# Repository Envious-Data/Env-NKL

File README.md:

# Env-NKL
A Keyboard without Nav Keys but has A numpad!.. therefore NKL = NavKeyLess

## About
I saw a coolermaster quickfire TK and thought, ok well I could make my own of a similar layout and see how people like it, It also lets me have navkeys and numpad in a board similar to TKL in width so we'll see.

The board is designed to fit SMD Nuts so ill likely solder those onto this board when I get around to ordering my own.

Ive yet to create the firmware but you'll see it in the Repo if I does
keep in mind all my README's dont get updated often.

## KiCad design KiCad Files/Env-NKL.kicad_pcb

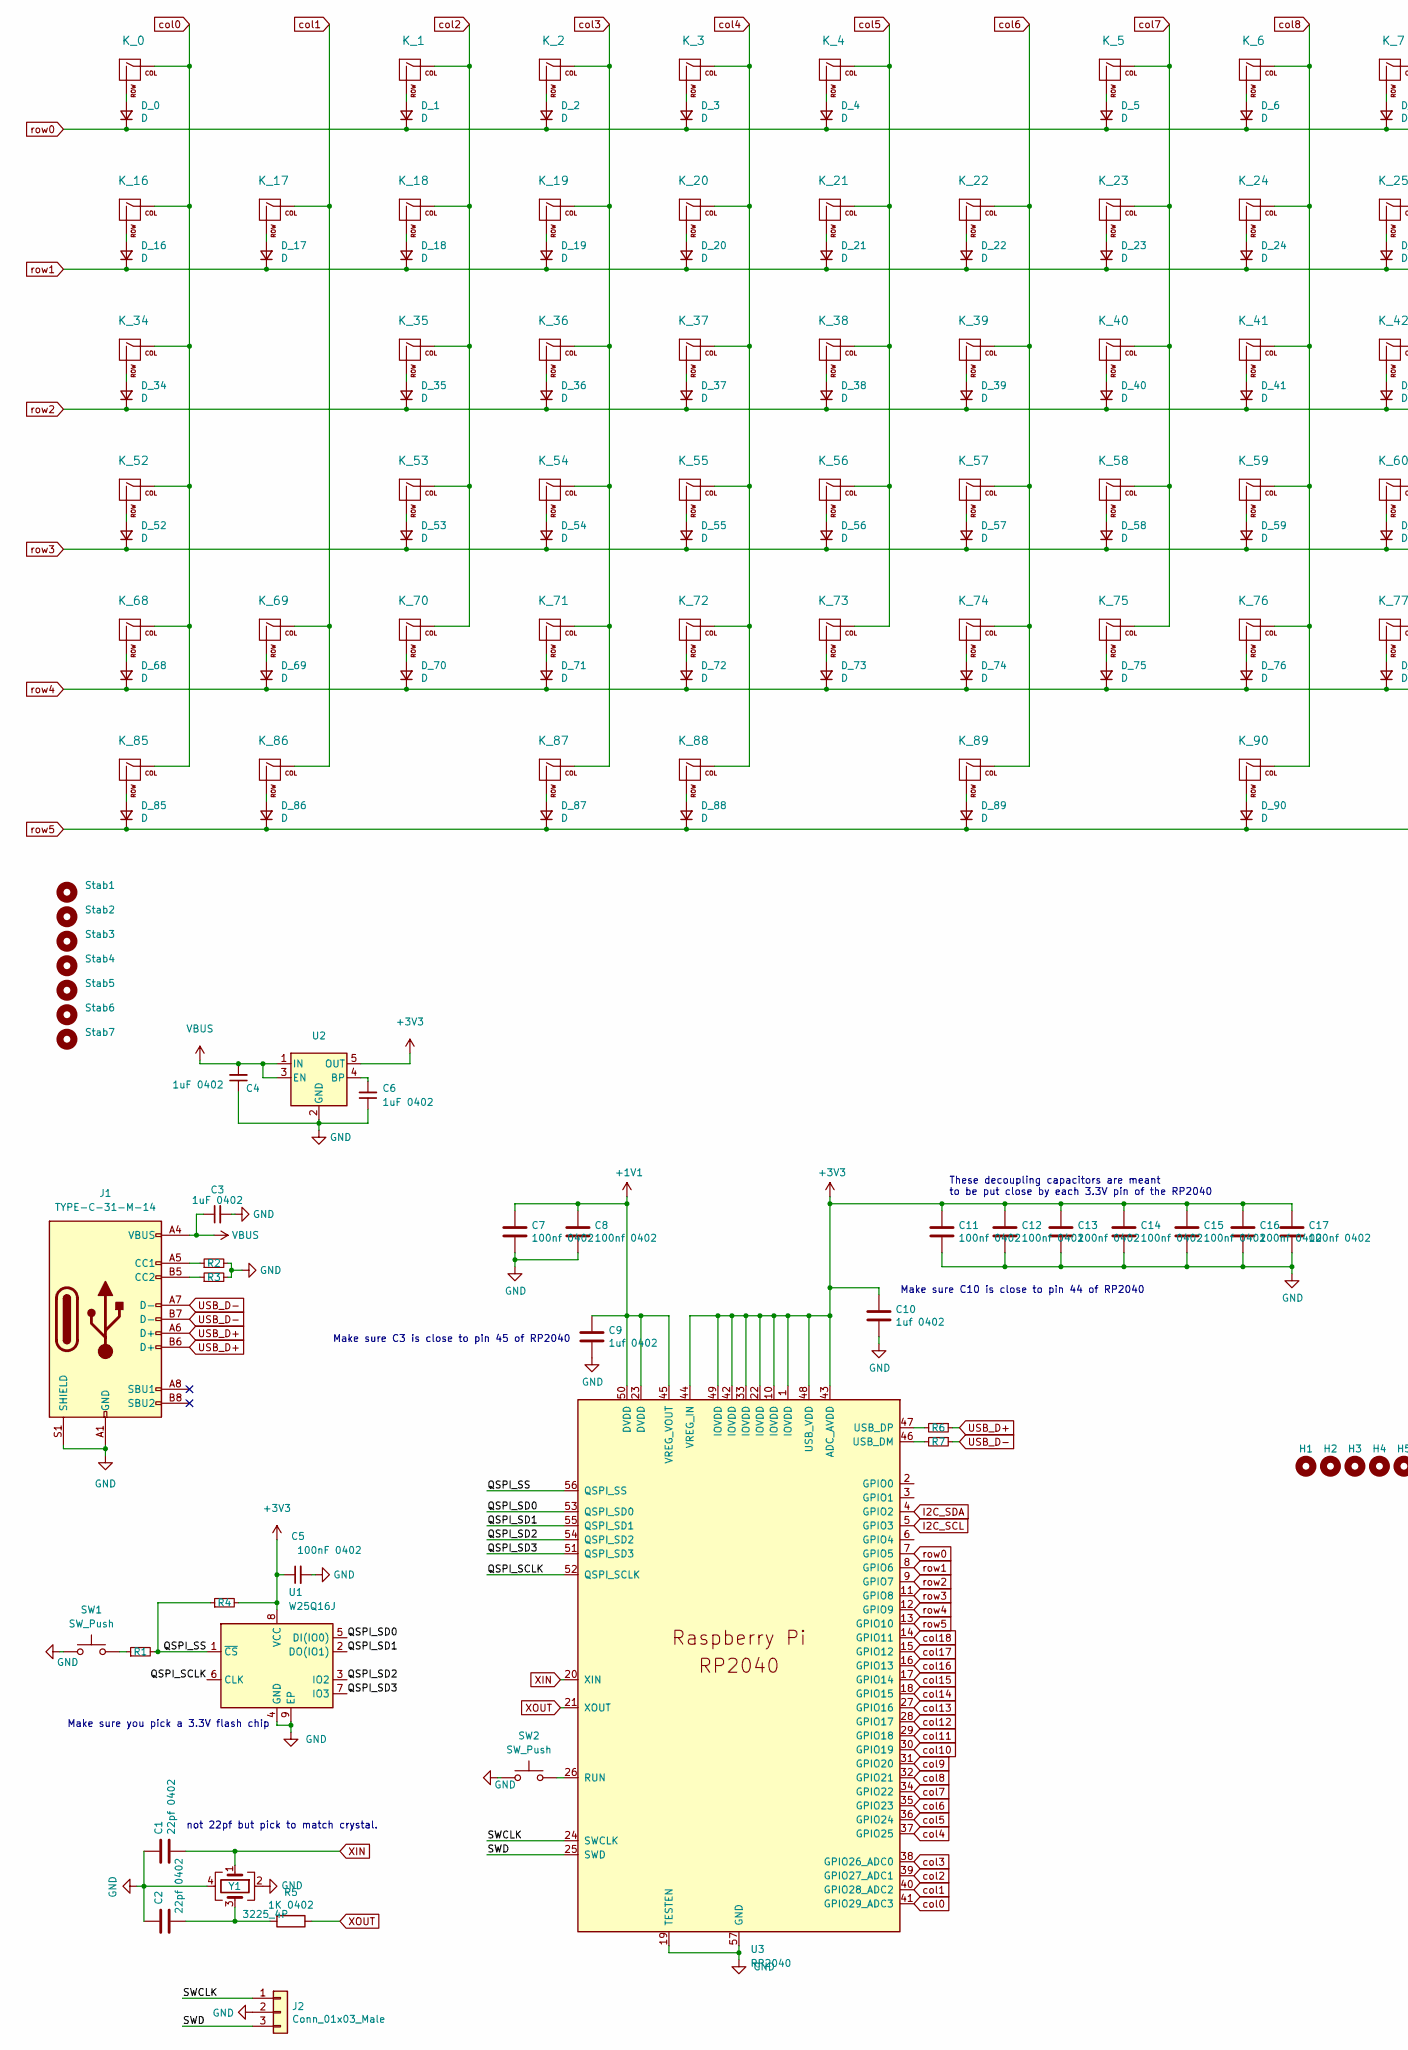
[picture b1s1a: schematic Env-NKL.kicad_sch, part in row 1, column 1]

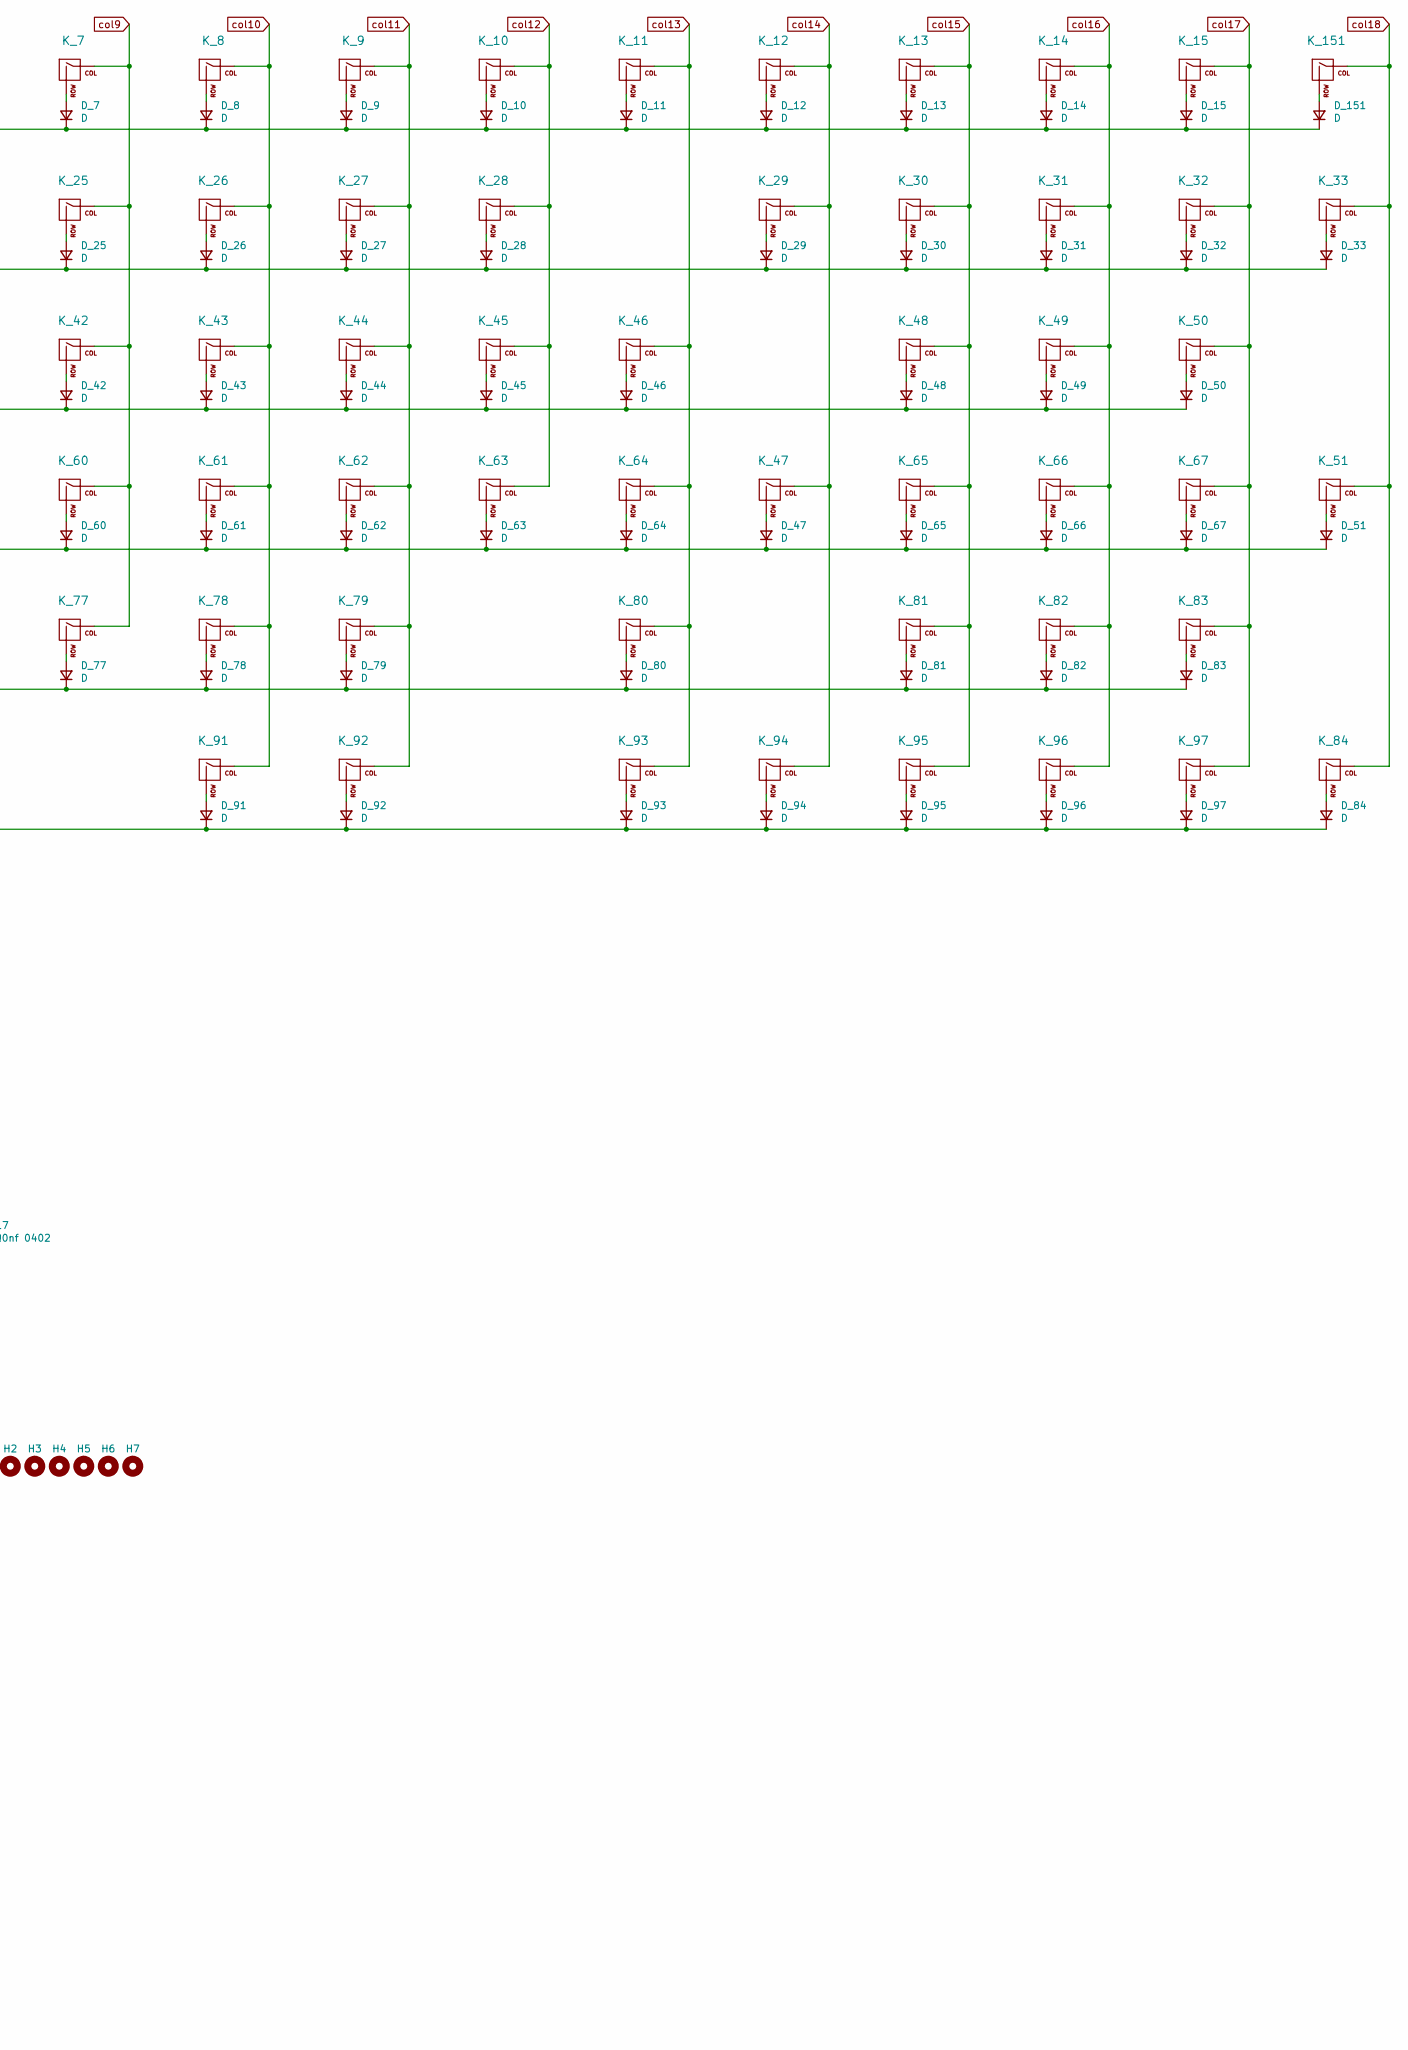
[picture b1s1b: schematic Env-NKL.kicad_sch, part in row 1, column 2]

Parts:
C1, C2: 22pf 0402; C_0402_1005Metric
C3, C4, C6: 1uF 0402; C_0402_1005Metric
C5: 100nF 0402; C_0402_1005Metric
C7, C8, C11, C12, C13, C14, C15, C16, C17: 100nf 0402; C_0402_1005Metric
C9, C10: 1uf 0402; C_0402_1005Metric
D_0, D_1, D_2, D_3, D_4, D_5, D_6, D_7, D_8, D_9, D_10, D_11, D_12, D_13, D_14, D_15, D_16, D_17, D_18, D_19, D_20, D_21, D_22, D_23, D_24, D_25, D_26, D_27, D_28, D_29, D_30, D_31, D_32, D_33, D_34, D_35, D_36, D_37, D_38, D_39, D_40, D_41, D_42, D_43, D_44, D_45, D_46, D_47, D_48, D_49, D_50, D_51, D_52, D_53, D_54, D_55, D_56, D_57, D_58, D_59, D_60, D_61, D_62, D_63, D_64, D_65, D_66, D_67, D_68, D_69, D_70, D_71, D_72, D_73, D_74, D_75, D_76, D_77, D_78, D_79, D_80, D_81, D_82, D_83, D_84, D_85, D_86, D_87, D_88, D_89, D_90, D_91, D_92, D_93, D_94, D_95, D_96, D_97, D_151: D; D_SOD-123
H1, H2, H3, H4, H5, H6, H7: MountingHole; MountingHole_2.2mm_M2_MODIFIED
J1: TYPE-C-31-M-14; USB_C_TYPE-C-31-M-14; MPN U262-161N-4BVC11; LCSC C319148
J2: Conn_01x03_Male; PinHeader_1x03_P2.54mm_Vertical
K_0, K_1, K_2, K_3, K_4, K_5, K_6, K_7, K_8, K_9, K_10, K_11, K_12, K_13, K_14, K_15, K_16, K_17, K_18, K_19, K_20, K_21, K_22, K_23, K_24, K_25, K_26, K_27, K_28, K_29, K_30, K_31, K_32, K_33, K_34, K_35, K_36, K_37, K_38, K_39, K_40, K_41, K_42, K_43, K_44, K_45, K_46, K_47, K_48, K_49, K_50, K_51, K_52, K_53, K_54, K_55, K_56, K_57, K_58, K_59, K_60, K_61, K_62, K_63, K_64, K_65, K_66, K_67, K_68, K_69, K_70, K_71, K_72, K_73, K_74, K_75, K_76, K_77, K_78, K_79, K_80, K_81, K_82, K_83, K_84, K_85, K_86, K_87, K_88, K_89, K_90, K_91, K_92, K_93, K_94, K_95, K_96, K_97, K_151: KEYSW; MXOnly-1U-NoLED
R1, R5: 1K 0402; R_0402_1005Metric
R2, R3: 5.1K 0402; R_0402_1005Metric
R4: 10K 0402; R_0402_1005Metric
R6, R7: 22 0402; R_0402_1005Metric
SW1, SW2: SW_Push; SW_Push_SPST_NO_Alps_SKRK
Stab1, Stab2, Stab3, Stab4, Stab5, Stab6, Stab7: MountingHole; Stabilizer_Cherry_MX_2u
U1: W25Q16J; SOIC-8_3.9x4.9mm_P1.27mm
U2: 3.3V SOT-23-5 5.5V 3.3V; SOT-23-5
U3: RP2040; RP2040-QFN-56
Y1: 3225_4P; Crystal_SMD_3225-4Pin_3.2x2.5mm

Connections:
+1V1: C7.1, C8.1, C9.1, U3.23 (DVDD), U3.45 (VREG_VOUT), U3.50 (DVDD)
+3V3: C5.1, C10.1, C11.1, C12.1, C13.1, C14.1, C15.1, C16.1, C17.1, R4.2, U1.8 (VCC), U2.5 (OUT), U3.1 (IOVDD), U3.10 (IOVDD), U3.22 (IOVDD), U3.33 (IOVDD), U3.42 (IOVDD), U3.43 (ADC_AVDD), U3.44 (VREG_IN), U3.48 (USB_VDD), U3.49 (IOVDD)
/QSPI_SCLK: U1.6 (CLK), U3.52 (QSPI_SCLK)
/QSPI_SD0: U1.5 (DI(IO0)), U3.53 (QSPI_SD0)
/QSPI_SD1: U1.2 (DO(IO1)), U3.55 (QSPI_SD1)
/QSPI_SD2: U1.3 (IO2), U3.54 (QSPI_SD2)
/QSPI_SD3: U1.7 (IO3), U3.51 (QSPI_SD3)
/QSPI_SS: R1.2, R4.1, U1.1 (~CS), U3.56 (QSPI_SS)
/SWCLK: J2.1, U3.24 (SWCLK)
/SWD: J2.3, U3.25 (SWD)
GND: C1.1, C2.1, C3.2, C4.1, C5.2, C6.1, C7.2, C8.2, C9.2, C10.2, C11.2, C12.2, C13.2, C14.2, C15.2, C16.2, C17.2, J1.A1 (GND), J1.A12 (GND), J1.B1 (GND), J1.B12 (GND), J1.S1 (SHIELD), J2.2, R2.2, R3.2, SW1.1, SW2.1, U1.4 (GND), U1.9 (EP), U2.2 (GND), U3.19 (TESTEN), U3.57 (GND), Y1.2, Y1.4
I2C_SCL: U3.5 (GPIO3)
I2C_SDA: U3.4 (GPIO2)
unnamed: C2.2, R5.2, Y1.3
unnamed: C6.2, U2.4 (BP)
unnamed: D_0.2 (A), K_0.2 (ROW)
unnamed: D_1.2 (A), K_1.2 (ROW)
unnamed: D_2.2 (A), K_2.2 (ROW)
unnamed: D_3.2 (A), K_3.2 (ROW)
unnamed: D_4.2 (A), K_4.2 (ROW)
unnamed: D_5.2 (A), K_5.2 (ROW)
unnamed: D_6.2 (A), K_6.2 (ROW)
unnamed: D_7.2 (A), K_7.2 (ROW)
unnamed: D_8.2 (A), K_8.2 (ROW)
unnamed: D_9.2 (A), K_9.2 (ROW)
unnamed: D_10.2 (A), K_10.2 (ROW)
unnamed: D_11.2 (A), K_11.2 (ROW)
unnamed: D_12.2 (A), K_12.2 (ROW)
unnamed: D_13.2 (A), K_13.2 (ROW)
unnamed: D_14.2 (A), K_14.2 (ROW)
unnamed: D_15.2 (A), K_15.2 (ROW)
unnamed: D_16.2 (A), K_16.2 (ROW)
unnamed: D_17.2 (A), K_17.2 (ROW)
unnamed: D_18.2 (A), K_18.2 (ROW)
unnamed: D_19.2 (A), K_19.2 (ROW)
unnamed: D_20.2 (A), K_20.2 (ROW)
unnamed: D_21.2 (A), K_21.2 (ROW)
unnamed: D_22.2 (A), K_22.2 (ROW)
unnamed: D_23.2 (A), K_23.2 (ROW)
unnamed: D_24.2 (A), K_24.2 (ROW)
unnamed: D_25.2 (A), K_25.2 (ROW)
unnamed: D_26.2 (A), K_26.2 (ROW)
unnamed: D_27.2 (A), K_27.2 (ROW)
unnamed: D_28.2 (A), K_28.2 (ROW)
unnamed: D_29.2 (A), K_29.2 (ROW)
unnamed: D_30.2 (A), K_30.2 (ROW)
unnamed: D_31.2 (A), K_31.2 (ROW)
unnamed: D_32.2 (A), K_32.2 (ROW)
unnamed: D_33.2 (A), K_33.2 (ROW)
unnamed: D_34.2 (A), K_34.2 (ROW)
unnamed: D_35.2 (A), K_35.2 (ROW)
unnamed: D_36.2 (A), K_36.2 (ROW)
unnamed: D_37.2 (A), K_37.2 (ROW)
unnamed: D_38.2 (A), K_38.2 (ROW)
unnamed: D_39.2 (A), K_39.2 (ROW)
unnamed: D_40.2 (A), K_40.2 (ROW)
unnamed: D_41.2 (A), K_41.2 (ROW)
unnamed: D_42.2 (A), K_42.2 (ROW)
unnamed: D_43.2 (A), K_43.2 (ROW)
unnamed: D_44.2 (A), K_44.2 (ROW)
unnamed: D_45.2 (A), K_45.2 (ROW)
unnamed: D_46.2 (A), K_46.2 (ROW)
unnamed: D_47.2 (A), K_47.2 (ROW)
unnamed: D_48.2 (A), K_48.2 (ROW)
unnamed: D_49.2 (A), K_49.2 (ROW)
unnamed: D_50.2 (A), K_50.2 (ROW)
unnamed: D_51.2 (A), K_51.2 (ROW)
unnamed: D_52.2 (A), K_52.2 (ROW)
unnamed: D_53.2 (A), K_53.2 (ROW)
unnamed: D_54.2 (A), K_54.2 (ROW)
unnamed: D_55.2 (A), K_55.2 (ROW)
unnamed: D_56.2 (A), K_56.2 (ROW)
unnamed: D_57.2 (A), K_57.2 (ROW)
unnamed: D_58.2 (A), K_58.2 (ROW)
unnamed: D_59.2 (A), K_59.2 (ROW)
unnamed: D_60.2 (A), K_60.2 (ROW)
unnamed: D_61.2 (A), K_61.2 (ROW)
unnamed: D_62.2 (A), K_62.2 (ROW)
unnamed: D_63.2 (A), K_63.2 (ROW)
unnamed: D_64.2 (A), K_64.2 (ROW)
unnamed: D_65.2 (A), K_65.2 (ROW)
unnamed: D_66.2 (A), K_66.2 (ROW)
unnamed: D_67.2 (A), K_67.2 (ROW)
unnamed: D_68.2 (A), K_68.2 (ROW)
unnamed: D_69.2 (A), K_69.2 (ROW)
unnamed: D_70.2 (A), K_70.2 (ROW)
unnamed: D_71.2 (A), K_71.2 (ROW)
unnamed: D_72.2 (A), K_72.2 (ROW)
unnamed: D_73.2 (A), K_73.2 (ROW)
unnamed: D_74.2 (A), K_74.2 (ROW)
unnamed: D_75.2 (A), K_75.2 (ROW)
unnamed: D_76.2 (A), K_76.2 (ROW)
unnamed: D_77.2 (A), K_77.2 (ROW)
unnamed: D_78.2 (A), K_78.2 (ROW)
unnamed: D_79.2 (A), K_79.2 (ROW)
unnamed: D_80.2 (A), K_80.2 (ROW)
unnamed: D_81.2 (A), K_81.2 (ROW)
unnamed: D_82.2 (A), K_82.2 (ROW)
unnamed: D_83.2 (A), K_83.2 (ROW)
unnamed: D_84.2 (A), K_84.2 (ROW)
unnamed: D_85.2 (A), K_85.2 (ROW)
unnamed: D_86.2 (A), K_86.2 (ROW)
unnamed: D_87.2 (A), K_87.2 (ROW)
unnamed: D_88.2 (A), K_88.2 (ROW)
unnamed: D_89.2 (A), K_89.2 (ROW)
unnamed: D_90.2 (A), K_90.2 (ROW)
unnamed: D_91.2 (A), K_91.2 (ROW)
unnamed: D_92.2 (A), K_92.2 (ROW)
unnamed: D_93.2 (A), K_93.2 (ROW)
unnamed: D_94.2 (A), K_94.2 (ROW)
unnamed: D_95.2 (A), K_95.2 (ROW)
unnamed: D_96.2 (A), K_96.2 (ROW)
unnamed: D_97.2 (A), K_97.2 (ROW)
unnamed: D_151.2 (A), K_151.2 (ROW)
unnamed: J1.A5 (CC1), R2.1
unnamed: J1.B5 (CC2), R3.1
unnamed: R1.1, SW1.2
unnamed: R6.2, U3.47 (USB_DP)
unnamed: R7.2, U3.46 (USB_DM)
unnamed: SW2.2, U3.26 (RUN)
USB_D+: J1.A6 (D+), J1.B6 (D+), R6.1
USB_D-: J1.A7 (D-), J1.B7 (D-), R7.1
VBUS: C3.1, C4.2, J1.A4 (VBUS), J1.A9 (VBUS), J1.B4 (VBUS), J1.B9 (VBUS), U2.1 (IN), U2.3 (EN)
XIN: C1.2, U3.20 (XIN), Y1.1
XOUT: R5.1, U3.21 (XOUT)
col0: K_0.1 (COL), K_16.1 (COL), K_34.1 (COL), K_52.1 (COL), K_68.1 (COL), K_85.1 (COL), U3.41 (GPIO29_ADC3)
col1: K_17.1 (COL), K_69.1 (COL), K_86.1 (COL), U3.40 (GPIO28_ADC2)
col2: K_1.1 (COL), K_18.1 (COL), K_35.1 (COL), K_53.1 (COL), K_70.1 (COL), U3.39 (GPIO27_ADC1)
col3: K_2.1 (COL), K_19.1 (COL), K_36.1 (COL), K_54.1 (COL), K_71.1 (COL), K_87.1 (COL), U3.38 (GPIO26_ADC0)
col4: K_3.1 (COL), K_20.1 (COL), K_37.1 (COL), K_55.1 (COL), K_72.1 (COL), K_88.1 (COL), U3.37 (GPIO25)
col5: K_4.1 (COL), K_21.1 (COL), K_38.1 (COL), K_56.1 (COL), K_73.1 (COL), U3.36 (GPIO24)
col6: K_22.1 (COL), K_39.1 (COL), K_57.1 (COL), K_74.1 (COL), K_89.1 (COL), U3.35 (GPIO23)
col7: K_5.1 (COL), K_23.1 (COL), K_40.1 (COL), K_58.1 (COL), K_75.1 (COL), U3.34 (GPIO22)
col8: K_6.1 (COL), K_24.1 (COL), K_41.1 (COL), K_59.1 (COL), K_76.1 (COL), K_90.1 (COL), U3.32 (GPIO21)
col9: K_7.1 (COL), K_25.1 (COL), K_42.1 (COL), K_60.1 (COL), K_77.1 (COL), U3.31 (GPIO20)
col10: K_8.1 (COL), K_26.1 (COL), K_43.1 (COL), K_61.1 (COL), K_78.1 (COL), K_91.1 (COL), U3.30 (GPIO19)
col11: K_9.1 (COL), K_27.1 (COL), K_44.1 (COL), K_62.1 (COL), K_79.1 (COL), K_92.1 (COL), U3.29 (GPIO18)
col12: K_10.1 (COL), K_28.1 (COL), K_45.1 (COL), K_63.1 (COL), U3.28 (GPIO17)
col13: K_11.1 (COL), K_46.1 (COL), K_64.1 (COL), K_80.1 (COL), K_93.1 (COL), U3.27 (GPIO16)
col14: K_12.1 (COL), K_29.1 (COL), K_47.1 (COL), K_94.1 (COL), U3.18 (GPIO15)
col15: K_13.1 (COL), K_30.1 (COL), K_48.1 (COL), K_65.1 (COL), K_81.1 (COL), K_95.1 (COL), U3.17 (GPIO14)
col16: K_14.1 (COL), K_31.1 (COL), K_49.1 (COL), K_66.1 (COL), K_82.1 (COL), K_96.1 (COL), U3.16 (GPIO13)
col17: K_15.1 (COL), K_32.1 (COL), K_50.1 (COL), K_67.1 (COL), K_83.1 (COL), K_97.1 (COL), U3.15 (GPIO12)
col18: K_33.1 (COL), K_51.1 (COL), K_84.1 (COL), K_151.1 (COL), U3.14 (GPIO11)
row0: D_0.1 (K), D_1.1 (K), D_2.1 (K), D_3.1 (K), D_4.1 (K), D_5.1 (K), D_6.1 (K), D_7.1 (K), D_8.1 (K), D_9.1 (K), D_10.1 (K), D_11.1 (K), D_12.1 (K), D_13.1 (K), D_14.1 (K), D_15.1 (K), D_151.1 (K), U3.7 (GPIO5)
row1: D_16.1 (K), D_17.1 (K), D_18.1 (K), D_19.1 (K), D_20.1 (K), D_21.1 (K), D_22.1 (K), D_23.1 (K), D_24.1 (K), D_25.1 (K), D_26.1 (K), D_27.1 (K), D_28.1 (K), D_29.1 (K), D_30.1 (K), D_31.1 (K), D_32.1 (K), D_33.1 (K), U3.8 (GPIO6)
row2: D_34.1 (K), D_35.1 (K), D_36.1 (K), D_37.1 (K), D_38.1 (K), D_39.1 (K), D_40.1 (K), D_41.1 (K), D_42.1 (K), D_43.1 (K), D_44.1 (K), D_45.1 (K), D_46.1 (K), D_48.1 (K), D_49.1 (K), D_50.1 (K), U3.9 (GPIO7)
row3: D_47.1 (K), D_51.1 (K), D_52.1 (K), D_53.1 (K), D_54.1 (K), D_55.1 (K), D_56.1 (K), D_57.1 (K), D_58.1 (K), D_59.1 (K), D_60.1 (K), D_61.1 (K), D_62.1 (K), D_63.1 (K), D_64.1 (K), D_65.1 (K), D_66.1 (K), D_67.1 (K), U3.11 (GPIO8)
row4: D_68.1 (K), D_69.1 (K), D_70.1 (K), D_71.1 (K), D_72.1 (K), D_73.1 (K), D_74.1 (K), D_75.1 (K), D_76.1 (K), D_77.1 (K), D_78.1 (K), D_79.1 (K), D_80.1 (K), D_81.1 (K), D_82.1 (K), D_83.1 (K), U3.12 (GPIO9)
row5: D_84.1 (K), D_85.1 (K), D_86.1 (K), D_87.1 (K), D_88.1 (K), D_89.1 (K), D_90.1 (K), D_91.1 (K), D_92.1 (K), D_93.1 (K), D_94.1 (K), D_95.1 (K), D_96.1 (K), D_97.1 (K), U3.13 (GPIO10)

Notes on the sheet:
Make sure you pick a 3.3V flash chip
Make sure C10 is close to pin 44 of RP2040
Make sure C3 is close to pin 45 of RP2040
These decoupling capacitors are meant to be put close by each 3.3V pin of the RP2040
not 22pf but pick to match crystal.

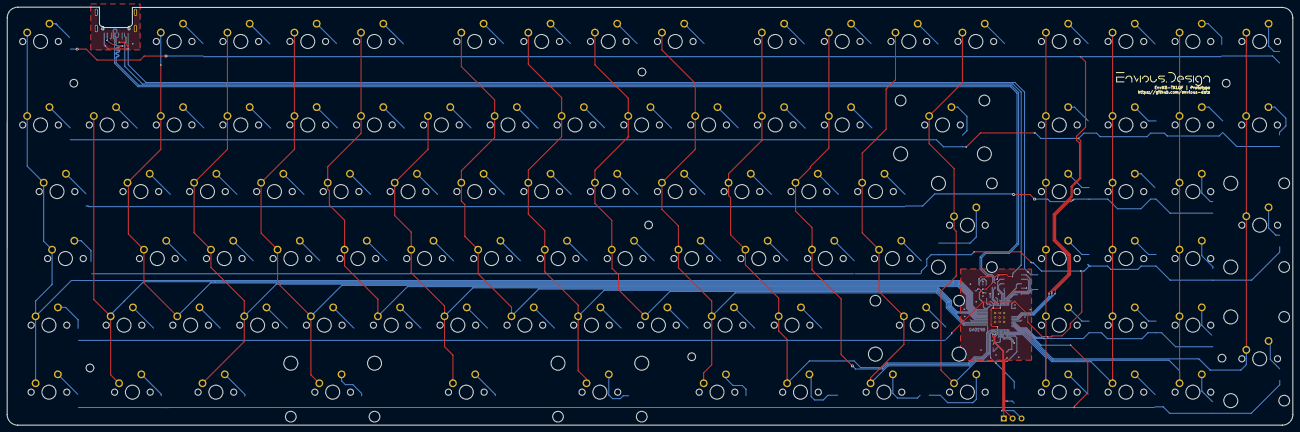
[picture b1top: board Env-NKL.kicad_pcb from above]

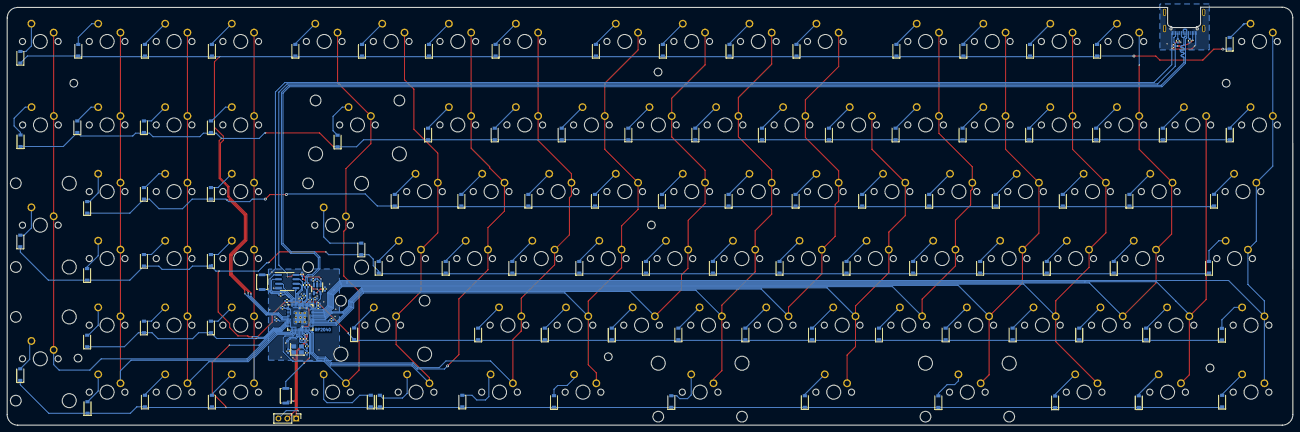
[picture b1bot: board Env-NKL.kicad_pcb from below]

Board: 2 copper layers, 366.6 x 119.2 mm, 245 parts (131 on the bottom side), 148 nets.

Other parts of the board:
kibuzzard-62762412: G***; kibuzzard-62762412

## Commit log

2022-07-25 Initial Commit+1
2022-07-29 named files properly
2022-10-07 changed button footprint so its easier to reset
2022-11-16 improved clearances and fixed issues regarding, made mount holes useable with SMD nuts.
2022-11-16 some small fixes and adjustments I missed
2022-11-16 generated step and updated readme
2023-02-10 Made backplate and moved mainPCB to its own folder
2023-02-10 removed some unnecessary files
2023-02-10 generated gerber for backplate
2023-02-13 experimenting & some curiosities with KiCad 7
2024-10-15 swapped board to hotswap, added ANSI keys and re-drew all traces, moved MCU and supporting components to accommodate new stabilisers and switches.
2024-10-16 Generated combined switchplate
2024-10-16 checked alignment and updated incorrect silkscreen.
2024-10-16 Generated production files for all boards.
2024-10-16 adjusted some traces and added a silkscreen notice.
2024-10-17 couple small fixes to clearances.
